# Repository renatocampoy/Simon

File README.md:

# Simon Says Baby
Mini Retro Games

Jogo da memória desenvolvido com intuito pedagógico.

Desenvolvido com o micro-controlador ATtiny85, no reprositorio você vai encontrar o projeto desenvolvido no Kicad, gabbers e códigos fontes, use da forma que achar melhor, só cite a fonte por favor.

### Duvidas e sujestões: campoytech@gmail.com 
Siga: https://www.instagram.com/campoytech

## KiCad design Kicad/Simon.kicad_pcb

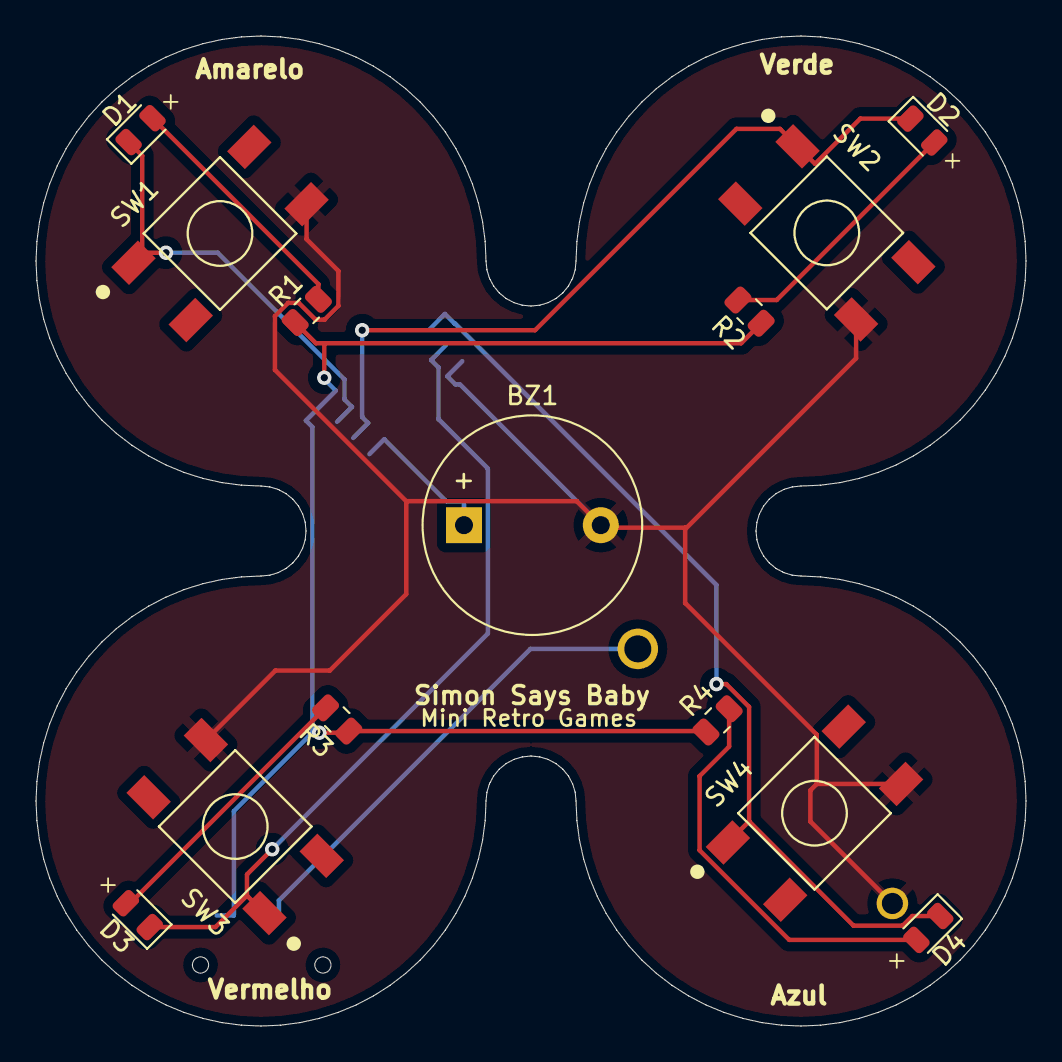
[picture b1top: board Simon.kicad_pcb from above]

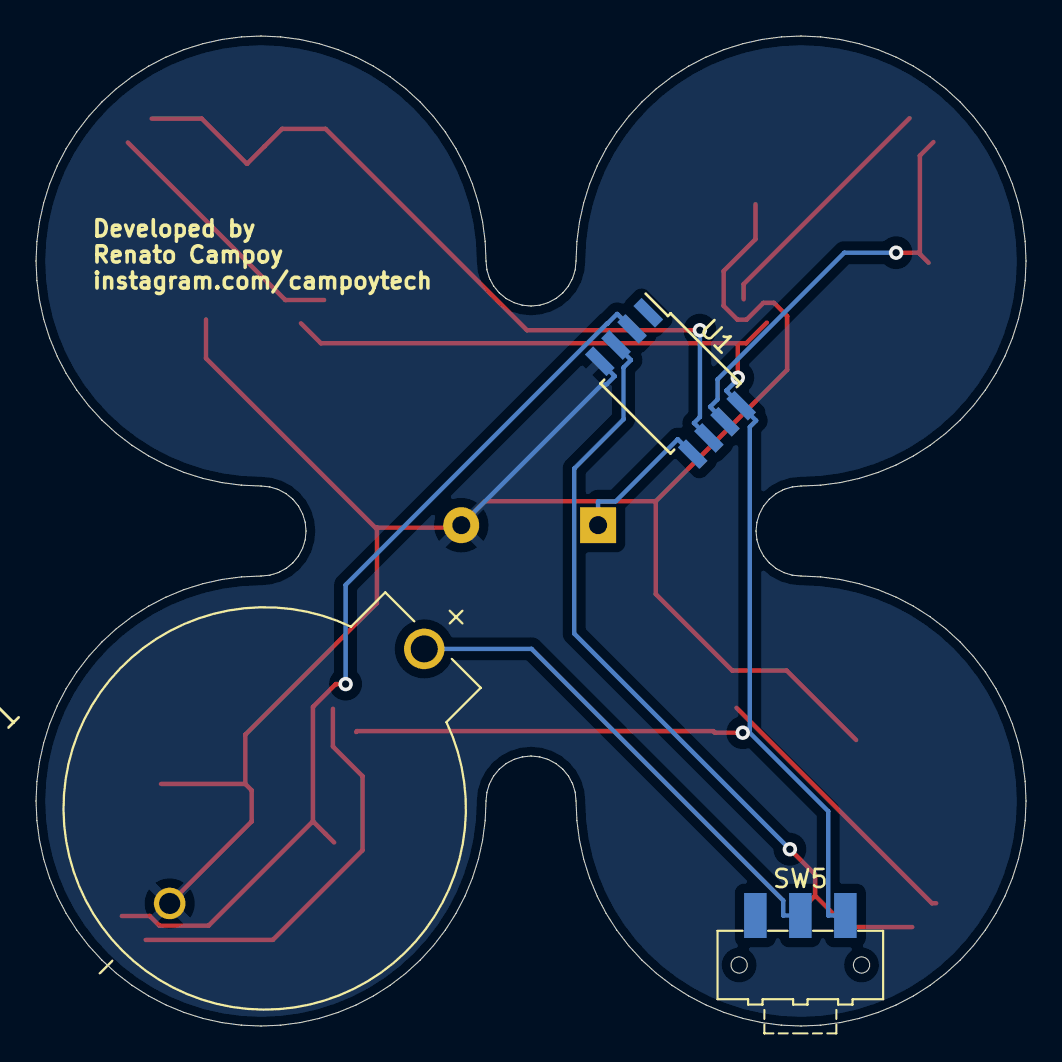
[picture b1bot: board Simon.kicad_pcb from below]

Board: 2 copper layers, 55.0 x 55.0 mm, 16 parts (3 on the bottom side), 12 nets.

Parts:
BZ1: Buzzer; Buzzer_12x9.5RM7.6
D1, D2, D3, D4: LED; LED_0805_2012Metric
J1: Bateria; BAT_BS-7
R1, R2, R3, R4: 150; R_0805_2012Metric
SW1, SW2, SW3, SW4: SW_Push; SW_5-1437565-0
SW5: SW_SPDT; SW_SPDT_CK-JS102011SAQN
U1: ATtiny85-20S; SOIC-8W_5.3x5.3mm_P1.27mm

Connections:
GND: BZ1.2 (+), J1.-, SW1.2, SW2.2, SW3.2, SW4.2, U1.4 (GND)
unnamed: BZ1.1 (-), U1.5 (AREF/PB0)
unnamed: D1.1 (K), SW1.1, U1.7 (PB2)
unnamed: D1.2 (A), R1.2
unnamed: D2.2 (A), R2.2
unnamed: D3.2 (A), R3.2
unnamed: D4.2 (A), R4.2
unnamed: R1.1, R2.1, R3.1, R4.1, SW5.3 (C), U1.8 (VCC)
unnamed: D4.1 (K), SW4.1, U1.2 (XTAL1/PB3)
unnamed: D3.1 (K), SW3.1, U1.3 (XTAL2/PB4)
unnamed: D2.1 (K), SW2.1, U1.6 (PB1)
VCC: J1.+, SW5.2 (B)

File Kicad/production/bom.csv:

Designator,Footprint,Quantity,Value,LCSC Part #
SW2,SW_5-1437565-0,1,SW_Push,
R1,R_0805_2012Metric,1,150,
BZ1,Buzzer_12x9.5RM7.6,1,Buzzer,
D3,LED_0805_2012Metric,1,LED,
SW4,SW_5-1437565-0,1,SW_Push,
R4,R_0805_2012Metric,1,150,
SW3,SW_5-1437565-0,1,SW_Push,
D2,LED_0805_2012Metric,1,LED,
SW1,SW_5-1437565-0,1,SW_Push,
D1,LED_0805_2012Metric,1,LED,
R3,R_0805_2012Metric,1,150,
D4,LED_0805_2012Metric,1,LED,
R2,R_0805_2012Metric,1,150,
J1,BAT_BS-7,1,Bateria,
SW5,SW_SPDT_CK-JS102011SAQN,1,SW_SPDT,
U1,SOIC-8W_5.3x5.3mm_P1.27mm,1,ATtiny85-20S,

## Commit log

2022-10-11 Primeiro envio
